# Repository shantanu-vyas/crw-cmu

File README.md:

crw-cmu
(Cooperative Robotic Watercraft)
http://code.google.com/p/crw-cmu/
Platypus LLC
=======

Small, autonomous watercraft are an ideal approach to a number of applications in flood mitigation and response, environmental sampling, and numerous other applications.

Relative to other types of vehicles, watercraft are inexpensive, simple, robust and reliable. Specifically, we are developing low cost airboats: flat-bottomed boats that use an above-water fan to propel themselves forward safely and effectively through shallow or debris-filled water.

The vision is to have large numbers of very inexpensive airboats provide situational awareness and deliver critical emergency supplies to victims, as well as low cost tools for environmental protection and monitoring. 

License (New BSD License)
=======
Copyright (c) <2013>, <Paul Scerri/Platypus LLC>
All rights reserved.

Redistribution and use in source and binary forms, with or without modification, are permitted provided that the following conditions are met:

    Redistributions of source code must retain the above copyright notice, this list of conditions and the following disclaimer.
    Redistributions in binary form must reproduce the above copyright notice, this list of conditions and the following disclaimer in the documentation and/or other materials provided with the distribution.
    Neither the name of the <ORGANIZATION> nor the names of its contributors may be used to endorse or promote products derived from this software without specific prior written permission.

THIS SOFTWARE IS PROVIDED BY THE COPYRIGHT HOLDERS AND CONTRIBUTORS "AS IS" AND ANY EXPRESS OR IMPLIED WARRANTIES, INCLUDING, BUT NOT LIMITED TO, THE IMPLIED WARRANTIES OF MERCHANTABILITY AND FITNESS FOR A PARTICULAR PURPOSE ARE DISCLAIMED. IN NO EVENT SHALL THE COPYRIGHT HOLDER OR CONTRIBUTORS BE LIABLE FOR ANY DIRECT, INDIRECT, INCIDENTAL, SPECIAL, EXEMPLARY, OR CONSEQUENTIAL DAMAGES (INCLUDING, BUT NOT LIMITED TO, PROCUREMENT OF SUBSTITUTE GOODS OR SERVICES; LOSS OF USE, DATA, OR PROFITS; OR BUSINESS INTERRUPTION) HOWEVER CAUSED AND ON ANY THEORY OF LIABILITY, WHETHER IN CONTRACT, STRICT LIABILITY, OR TORT (INCLUDING NEGLIGENCE OR OTHERWISE) ARISING IN ANY WAY OUT OF THE USE OF THIS SOFTWARE, EVEN IF ADVISED OF THE POSSIBILITY OF SUCH DAMAGE.

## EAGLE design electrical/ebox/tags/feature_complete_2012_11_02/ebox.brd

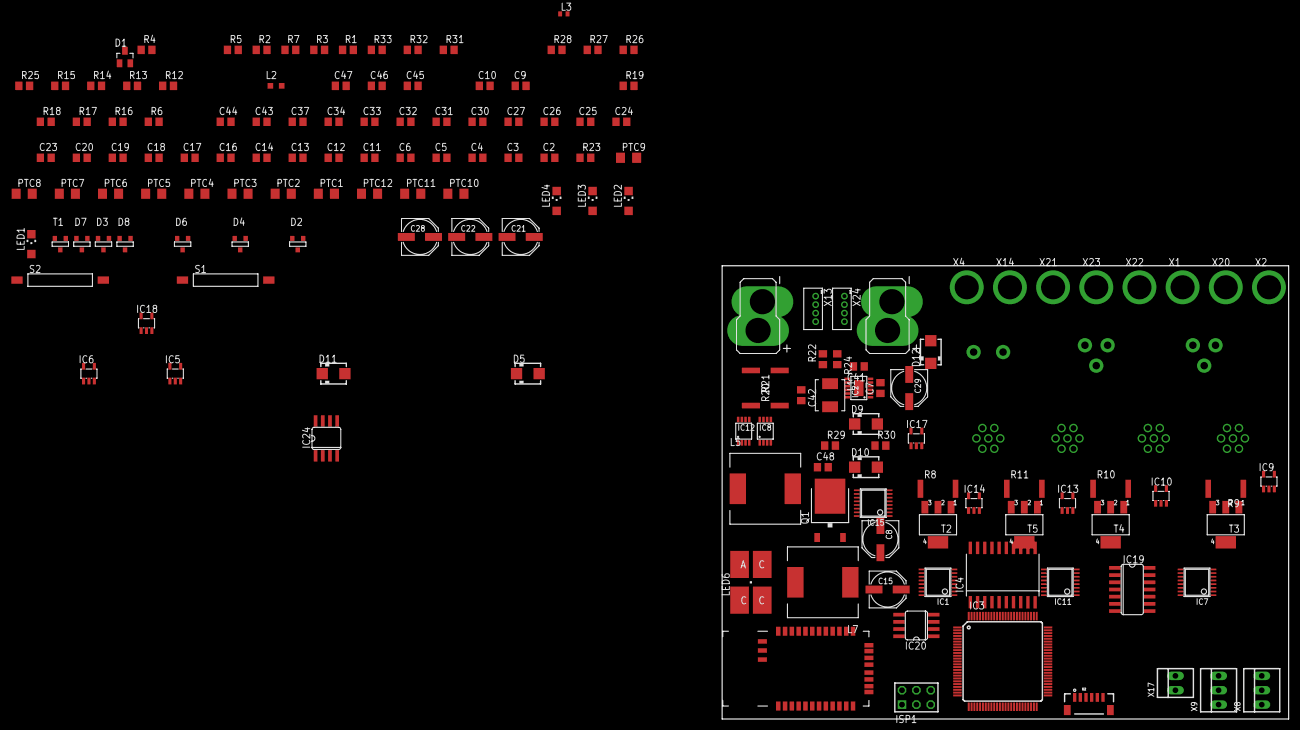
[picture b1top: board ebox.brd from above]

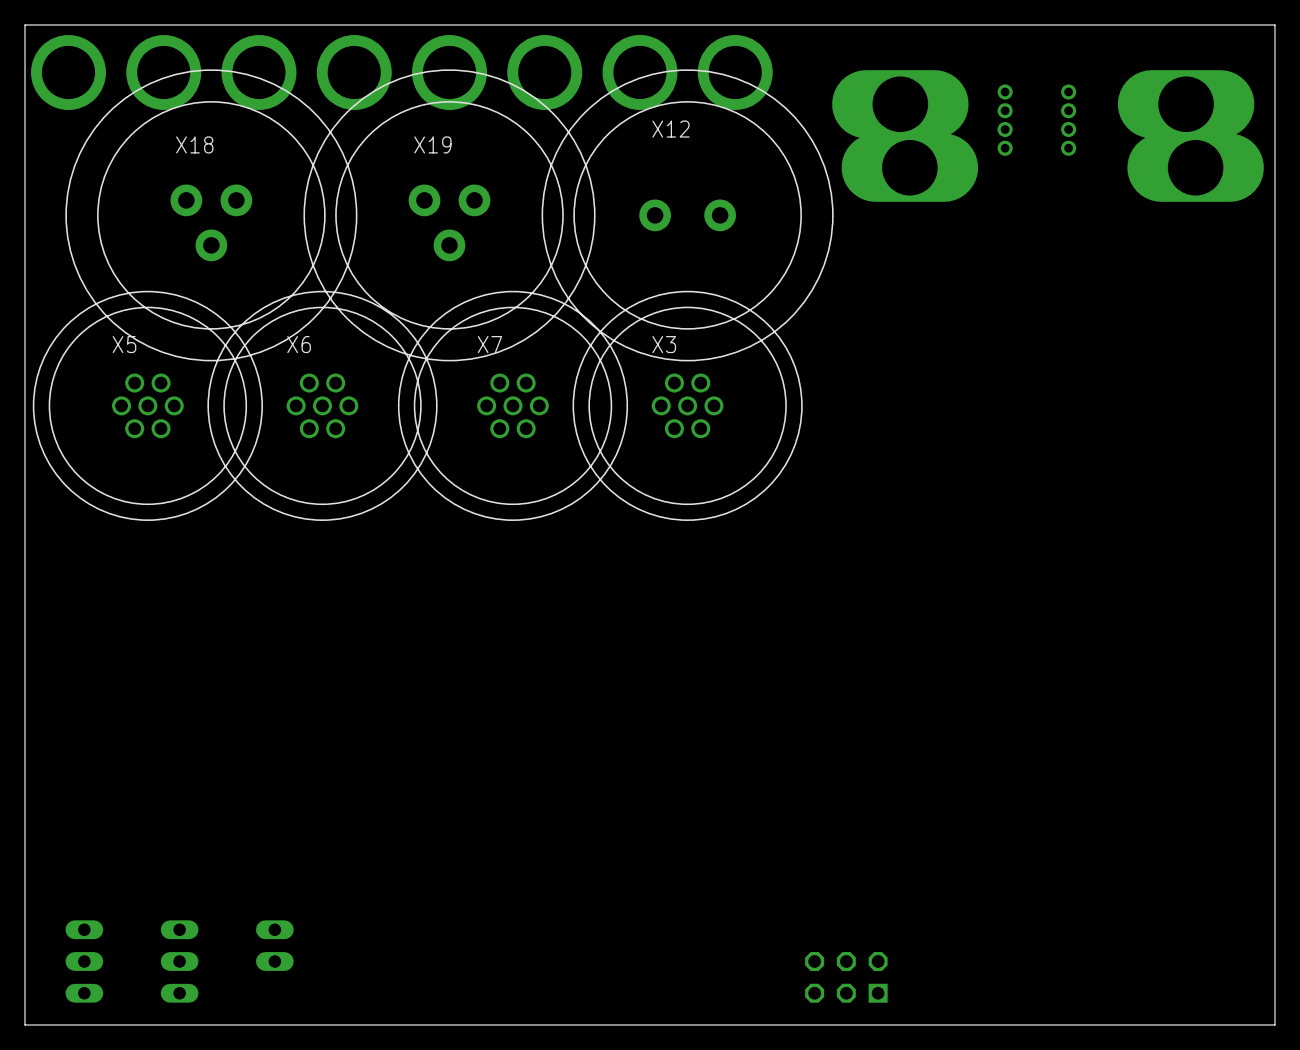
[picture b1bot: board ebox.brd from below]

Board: 2 copper layers, 100.0 x 80.0 mm, 162 parts (7 on the bottom side), 156 nets, no tracks yet.

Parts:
C2, C3, C4, C5, C6, C11, C12, C13, C14, C16, C17, C18, C19, C20, C23, C24, C25, C26, C27, C30, C31, C32, C33, C34, C37, C43, C44: 0.1uF; C0805
C7, C42: 1uF; C0805
C8, C15, C21, C29: 68uF; PANASONIC_D
C9, C10, C41, C47: 10uF; C0805
C22, C28: 220uF; PANASONIC_D
C45, C46, C48: 10pF; C0805
D1: SOT23
D2, D4, D6, D8: GSOT05C; SOT-23
D3, D7: SOT-23
D5, D9, D10, D11, D12: MBRA340T3; SMA
IC1, IC7, IC11, IC15: MAX3221CUE; TSSOP16
IC2: LT3652; MSOP12-MSE
IC3: XMEGA128A1; TQFP100
IC4: LT1161; SOIC20R
IC5, IC6, IC9, IC10, IC13, IC14, IC17, IC18: SN74LVC1G125; SOT23-DBV
IC8, IC12: INA170; MSOP8
IC19: 74ALS04D; SO14
IC20: AP1509-33; SO08
IC24: AP1509-5; SO08
ISP1: AVR-PDIVERT; AVR-ISP-6
L1: 5.6uH; IHLP-2020CZ-11
L2: 10uH; L2012C
L3: FERRITE; 0402
L5, L7: 47uH; SRR1280
LED1: YEL; CHIPLED_1206
LED2, LED4: RED; CHIPLED_1206
LED3: GRN; CHIPLED_1206
LED6: P-LCC-4
PTC1, PTC2, PTC3, PTC4, PTC5, PTC6, PTC7, PTC8: 50mA; R1206
PTC9, PTC10, PTC11, PTC12: 1A; R1206
Q1: FDD4141TO252; TO252
R1, R3, R7, R28, R31, R32, R33: 330; R0805
R2, R5, R27, R29: 10k; R0805
R4, R25: 1k; R0805
R6, R16, R17, R18, R19: 100k; R0805
R8, R9, R10, R11, R21: 0.010; R6332
R12, R13, R14, R15: 2K; R0805
R20: 0.050; R6332
R22: 626k; R0805
R23: 4.99k; R0805
R24: 412k; R0805
R26, R30: 2k; R0805
S1, S2: REED-SWITCH-CT10-1530-G1; CT10-G1
T1: SOT-23
T2, T3, T4, T5: SOT223
U1: BLUETOOTH-RN42; RN41
U2: D2523T_; EM406
X1, X2, X4, X14, X20, X21, X22, X23: BULLET
X3, X5, X6, X7: 17984-7PG-300
X8, X9: 22-23-2031
X10, X11: DEANS
X12: 7381-2PG-300
X13, X24: B4B-ZR
X17: 22-23-2021
X18, X19: 7381-3PG-300

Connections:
!CHRG: IC2.4, IC3.68
!CHRG_FAULT: IC2.5, IC3.67
!EN232_1: IC1.1, IC3.69, IC19.1
!EN232_2: IC3.70, IC7.1, IC19.3
!EN232_3: IC3.71, IC11.1, IC19.5
!EN232_4: IC3.72, IC15.1, IC19.9
+3V3: C6.1, C14.1, C20.1, C22.+, C27.1, C34.1, C37.1, C43.1, C44.1, C47.1, IC1.15, IC6.5, IC7.15, IC8.3, IC8.8, IC10.5, IC11.15, IC12.3, IC12.8, IC14.5, IC15.15, IC18.5, IC19.14, IC20.3, ISP1.2, L2.2, L7.2, LED6.A, R1.2, R2.2, R3.2, R7.2, R28.2, U1.11, U2.3
+5V: C28.+, IC24.3, L5.2, PTC9.1, PTC10.1, PTC11.1, PTC12.1
+12V: C8.+, C15.+, C21.+, IC4.11, IC4.20, IC20.1, IC24.1, Q1.3, R8.2, R9.2, R10.2, R11.2
AVR_AVCC: C10.1, C11.1, IC3.4, IC3.94, L3.1
AVR_VCC: C9.1, C12.1, IC3.14, IC3.24, IC3.34, IC3.44, IC3.54, IC3.64, IC3.74, IC3.83, L2.1, L3.2
BATT1: X13.2, X24.2
BATT2: X13.3, X24.3
BATT+: IC2.9, IC8.1, IC12.2, R20.2, R21.1, R22.2, R29.2, X10.POS, X11.POS, X13.4, X24.4
BATT-: X10.NEG, X11.NEG, X13.1, X24.1
BATT_CURR_IN: C45.1, IC3.95, IC8.6, R25.2
BATT_CURR_OUT: C46.1, IC3.96, IC12.6, R23.2
BATT_TEMP: IC2.8, IC3.97, X17.1
BATT_VSENSE: C48.1, IC3.98, R29.1, R30.2
BT_CTS: IC3.49, U1.16
BT_RESET: IC3.51, U1.5
BT_RTS: IC3.50, U1.15
BT_RXD: IC3.21, U1.14
BT_STATUS: IC3.52, U1.19
BT_TXD: IC3.22, U1.13
CHARGE: D12.A, X4.P$1, X12.1
CHRG+: D9.A, IC2.10, IC8.2, L1.2, R20.1
EN232_1: IC1.16, IC5.3, IC6.3, IC19.2
EN232_2: IC7.16, IC9.3, IC10.3, IC19.4
EN232_3: IC11.16, IC13.3, IC14.3, IC19.6
EN232_4: IC15.16, IC17.3, IC18.3, IC19.8
FAULT1: IC3.75, IC4.2, R12.2
FAULT2: IC3.77, IC4.4, R13.2
FAULT3: IC3.79, IC4.6, R14.2
FAULT4: IC3.81, IC4.8, R15.2
GND: C4.2, C5.1, C6.2, C7.2, C8.-, C9.2, C10.2, C11.2, C12.2, C14.2, C15.-, C18.2, C19.1, C20.2, C21.-, C22.-, C25.2, C26.1, C27.2, C28.-, C29.-, C32.2, C33.1, C34.2, C37.2, C41.2, C43.2, C44.2, C45.2, C46.2, C47.2, C48.2, D1.1, D2.1, D3.1, D4.1, D5.A, D6.1, D7.1, D8.1, D10.A, D11.A, IC1.14, IC2.13, IC3.3, IC3.13, IC3.23, IC3.33, IC3.43, IC3.53, IC3.63, IC3.73, IC3.84, IC3.93, IC4.1, IC4.10, IC5.2, IC6.2, IC7.14, IC8.4, IC9.2, IC10.2, IC11.14, IC12.4, IC13.2, IC14.2, IC15.14, IC17.2, IC18.2, IC19.7, IC19.11, IC19.13, IC20.4, IC20.5, IC20.6, IC20.7, IC20.8, IC24.4, IC24.5, IC24.6, IC24.7, IC24.8, ISP1.6, LED4.C, R23.1, R24.1, R25.1, R26.1, R27.1, R30.1, S1.2, S2.2, T1.1, U1.1, U1.12, U1.25, U1.27, U1.28, U1.29, U2.4, X3.7, X5.7, X6.7, X7.7, X8.3, X9.3, X12.2, X14.P$1, X17.2
GPIO1A: D2.2, IC3.5, IC3.25, PTC1.1
GPIO1B: D2.3, IC3.6, IC3.8, IC3.26, PTC2.1
GPIO2A: D4.2, IC3.7, IC3.29, PTC3.1
GPIO2B: D4.3, IC3.30, PTC4.1
GPIO3A: D6.2, IC3.9, IC3.35, PTC5.1
GPIO3B: D6.3, IC3.10, IC3.36, PTC6.1
GPIO4A: D8.2, IC3.11, IC3.39, PTC7.1
GPIO4B: D8.3, IC3.12, IC3.40, PTC8.1
GPS_RXD: IC3.17, U2.5
GPS_TXD: IC3.18, U2.6
LED_BLU: IC3.19, R32.1
LED_GRN: IC3.16, R33.1
LED_RED: IC3.15, R31.1
LED_STATUS: IC3.20, LED1.C
LED_STATUS1: LED2.C, U1.21
MOT1_A: X1.P$1, X18.1
MOT1_B: X2.P$1, X18.2
MOT1_C: X18.3, X20.P$1
MOT1_SIG: IC3.45, X8.1
MOT2_A: X19.1, X21.P$1
MOT2_B: X19.2, X22.P$1
MOT2_C: X19.3, X23.P$1
MOT2_SIG: IC3.46, X9.1
unnamed: C2.2, IC1.4
unnamed: C2.1, IC1.2
unnamed: C3.1, IC1.5
unnamed: C3.2, IC1.6
unnamed: IC3.90, ISP1.5, R2.1
unnamed: LED1.A, R3.1
unnamed: IC3.89, ISP1.1
unnamed: R5.2, T1.3
unnamed: LED2.A, R7.1
unnamed: C4.1, IC1.3
unnamed: C5.2, IC1.7
unnamed: IC4.19, R8.1, T2.2
unnamed: C13.2, Q1.1, R4.1, R6.2, S1.1, T1.2
unnamed: IC4.17, R9.1, T3.2
unnamed: IC4.15, R10.1, T4.2
unnamed: IC4.13, R11.1, T5.2
unnamed: IC4.18, T2.1
unnamed: IC4.16, T3.1
unnamed: IC4.14, T4.1
unnamed: IC4.12, T5.1
unnamed: C16.2, IC7.4
unnamed: C16.1, IC7.2
unnamed: C17.2, IC7.6
unnamed: C17.1, IC7.5
unnamed: C18.1, IC7.3
unnamed: C19.2, IC7.7
unnamed: C23.2, IC11.4
unnamed: C23.1, IC11.2
unnamed: C24.2, IC11.6
unnamed: C24.1, IC11.5
unnamed: C25.1, IC11.3
unnamed: C26.2, IC11.7
unnamed: C30.2, IC15.4
unnamed: C30.1, IC15.2
unnamed: C31.2, IC15.6
unnamed: C31.1, IC15.5
unnamed: C32.1, IC15.3
unnamed: C33.2, IC15.7
unnamed: C41.1, IC2.6
unnamed: D5.C, IC20.2, L7.1
unnamed: C42.2, D9.C, IC2.11
unnamed: C42.1, D10.C, IC2.12, L1.1
unnamed: LED3.C, U2.1
unnamed: IC2.7, R22.1, R24.2
unnamed: D11.C, IC24.2, L5.1
unnamed: LED4.A, R1.1
unnamed: C7.1, C29.+, D12.C, IC2.1, IC2.2, IC2.3
unnamed: IC8.5, R26.2
unnamed: IC12.5, R27.2
unnamed: LED3.A, R28.1
unnamed: LED6.C@3, R32.2
unnamed: LED6.C@1, R31.2
unnamed: LED6.C@4, R33.2
PWR_CTL: IC3.56, R5.1
PWR_CTL1: IC3.76, IC4.3, R12.1
PWR_CTL2: IC3.78, IC4.5, R13.1
PWR_CTL3: IC3.80, IC4.7, R14.1
PWR_CTL4: IC3.82, IC4.9, R15.1
PWR_SENSE: D1.3, IC3.57, R6.1
RX1_TTL: IC1.9, IC3.27, IC6.4
RX2_TTL: IC3.31, IC7.9, IC10.4
RX3_TTL: IC3.37, IC11.9, IC14.4
RX4_TTL: IC3.41, IC15.9, IC18.4
S1_5V: IC5.5, PTC9.2, X3.4
S1_12V: T2.3, X3.1
S1_GPIO_A: PTC1.2, X3.5
S1_GPIO_B: PTC2.2, X3.6
S1_RX: IC1.8, R16.2, X3.2
S1_RX_33V: D3.3, IC6.1, R16.1
S1_TX: IC1.13, IC5.4, X3.3
S2_5V: IC9.5, PTC10.2, X5.4
S2_12V: T3.3, X5.1
S2_GPIO_A: PTC3.2, X5.5
S2_GPIO_B: PTC4.2, X5.6
S2_RX: IC7.8, R17.2, X5.2
S2_RX_33V: D3.2, IC10.1, R17.1
S2_TX: IC7.13, IC9.4, X5.3
S3_5V: IC13.5, PTC11.2, X6.4
S3_12V: T4.3, X6.1
S3_GPIO_A: PTC5.2, X6.5
S3_GPIO_B: PTC6.2, X6.6
S3_RX: IC11.8, R18.2, X6.2
S3_RX_33V: D7.3, IC14.1, R18.1
S3_TX: IC11.13, IC13.4, X6.3
S4_5V: IC17.5, PTC12.2, X7.4
S4_12V: T5.3, X7.1
S4_GPIO_A: PTC7.2, X7.5
S4_GPIO_B: PTC8.2, X7.6
S4_RX: IC15.8, R19.2, X7.2
S4_RX_33V: D7.2, IC18.1, R19.1
S4_TX: IC15.13, IC17.4, X7.3
TX1_TTL: IC1.11, IC3.28, IC5.1
TX2_TTL: IC3.32, IC7.11, IC9.1
TX3_TTL: IC3.38, IC11.11, IC13.1
TX4_TTL: IC3.42, IC15.11, IC17.1
USER_BUTTON: IC3.55, S2.1
V+: C13.1, IC12.1, Q1.2, R4.2, R21.2

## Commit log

2013-07-17 adding client/trunk
2013-07-18 Added controller code
    Added code that will let left bumper let you go straight by turning
    left and right at a specific time
2013-07-18 Fixed a Bug
    Forgot to change a jar to the updated one, and had to add the jvm path
    for the so for the controller
2013-07-19 Added Controller Help
    Added a picture of the control system for the ps3 controller and the
    button the access it along with changing a path for making it easier to
    make the jar and run the enduser
2013-07-21 Work around for a bug
    Commented out code in the network utils class that will fix the hostname
    bug for now
2013-07-22 Fixed some stuff
    Uncommented alot of code that i commented trying to fix a bug, the bug
    is still there Q_Q
2013-07-22 PS3 Controller Help Button now works
    Had to fix the path for that so its universal and had to uncomment and
    move some folders around
2013-07-22 Getting rid of ds store files
2013-07-22 didnt delete the files Q_Q
    i suck at git
2013-07-26 Fixed hostname bug
2013-07-29 Control and Path for libs
    Testing different ways to control such as turning only going half - 75%
    to reduce oversteer
    Putting all the libs for the controller in a localized place so anyone
    with the project can use them (and run the project ;_;)
2013-07-29 Fixed some earlier workarounds
    Fixed some stuttering on the bars when using the joystick caused by the
    value trying to decrease when given input that should make it increase
2013-07-29 adding more controls and fixing stuttering
    1) joystick 1 now only goes from 25 - 75% for rudder
    2) joystick 2 will go from 25-75 but as a softcap will go slower after
    that
    3) fixed the image (still has an issue that i forgot to change, will do
    later)
2013-07-29 adding more dependencies that werent localized
2013-07-29 readme
2013-07-30 Adding code for using other buttons
    Added all the code to access the different buttons
    All joystick controls will only go to 25-75
2013-07-30 changed image
2013-08-02 updated controls
    Right trigger now also will accelerate to 40% and right bumper is
    overdrive
2013-08-02 Updated Controls
    Right trigger now will also accelerate to 40% and right bumper is
    overdrive
2013-08-05 Adding more stuff
    tests for the buttons
2013-08-12 Triangle now toggles autonomy

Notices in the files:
parts and their libraries:
SparkFun-RF: Licensing: CC v3.0 Share-Alike You are welcome to use this library for commercial purposes.
